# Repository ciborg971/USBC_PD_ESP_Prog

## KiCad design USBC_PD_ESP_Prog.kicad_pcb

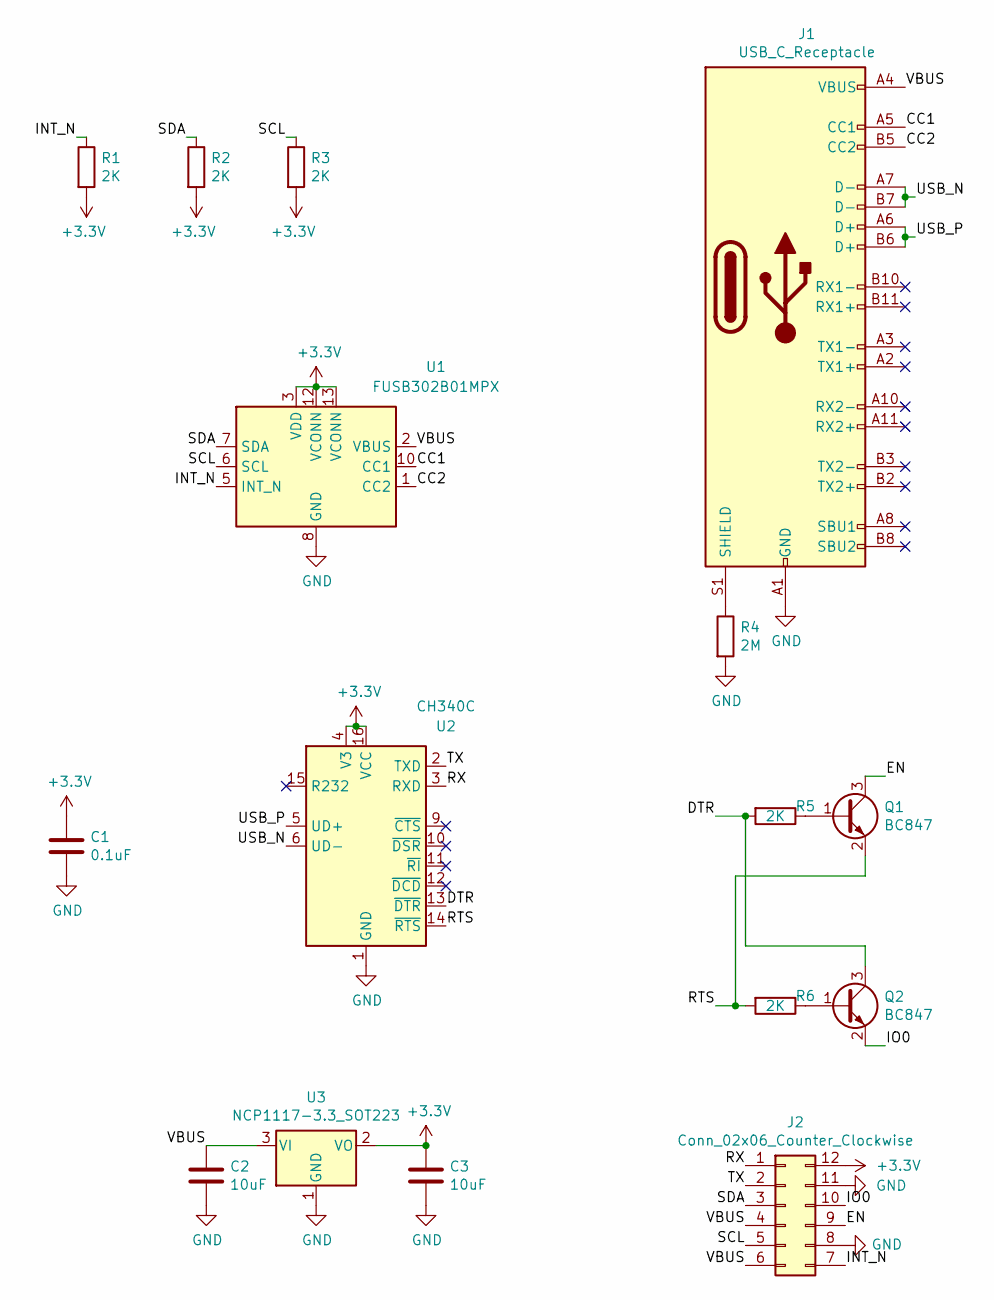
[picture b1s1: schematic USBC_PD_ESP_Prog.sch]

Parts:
C1: 0.1uF; C_0402_1005Metric
C2, C3: 10uF; C_0402_1005Metric
J1: USB_C_Receptacle; USB_C_Receptacle_Amphenol_12401610E4-2A
J2: Conn_02x06_Counter_Clockwise; PinHeader_2x06_P1.00mm_Vertical
Q1, Q2: BC847; SOT-23
R1, R2, R3, R5, R6: 2K; R_0201_0603Metric
R4: 2M; R_0201_0603Metric
U1: FUSB302B01MPX; WQFN-14-1EP_2.5x2.5mm_P0.5mm_EP1.45x1.45mm
U2: CH340C; SOIC-16_3.9x9.9mm_P1.27mm
U3: NCP1117-3.3_SOT223; SOT-223-3_TabPin2

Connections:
+3V3: C1.1, C3.1, J2.12, R1.2, R2.2, R3.2, U1.3 (VDD), U1.4 (VDD), U1.12 (VCONN), U1.13 (VCONN), U2.4 (V3), U2.16 (VCC), U3.2 (VO)
/CC1: J1.A5 (CC1), U1.10 (CC1), U1.11 (CC1)
/CC2: J1.B5 (CC2), U1.1 (CC2), U1.14 (CC2)
/DTR: Q2.3 (C), R5.2, U2.13 (~DTR)
/EN: J2.9, Q1.3 (C)
/INT_N: J2.7, R1.1, U1.5 (INT_N)
/IO0: J2.10, Q2.2 (E)
/RTS: Q1.2 (E), R6.2, U2.14 (~RTS)
/RX: J2.1, U2.3 (RXD)
/SCL: J2.5, R3.1, U1.6 (SCL)
/SDA: J2.3, R2.1, U1.7 (SDA)
/TX: J2.2, U2.2 (TXD)
/USB_N: J1.A7 (D-), J1.B7 (D-), U2.6 (UD-)
/USB_P: J1.A6 (D+), J1.B6 (D+), U2.5 (UD+)
/VBUS: C2.1, J1.A4 (VBUS), J1.A9 (VBUS), J1.B4 (VBUS), J1.B9 (VBUS), J2.4, J2.6, U1.2 (VBUS), U3.3 (VI)
GND: C1.2, C2.2, C3.2, J1.A1 (GND), J1.A12 (GND), J1.B1 (GND), J1.B12 (GND), J2.8, J2.11, R4.2, U1.8 (GND), U1.9 (GND), U1.15 (GND), U2.1 (GND), U3.1 (GND)
unnamed: J1.S1 (SHIELD), R4.1
unnamed: Q1.1 (B), R5.1
unnamed: Q2.1 (B), R6.1

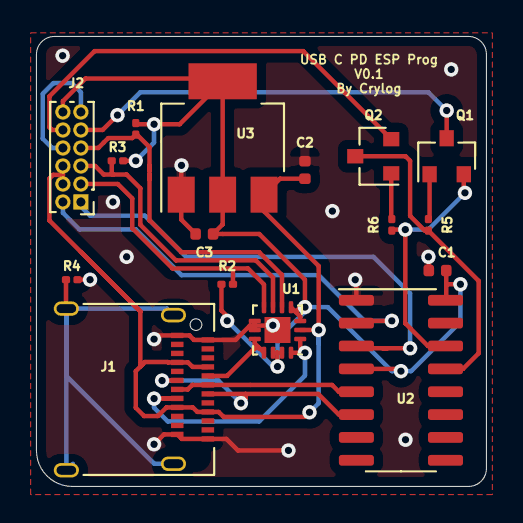
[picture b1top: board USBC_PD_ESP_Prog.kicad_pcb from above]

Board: 2 copper layers, 25.0 x 25.0 mm, 16 parts (0 on the bottom side), 19 nets.

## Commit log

2021-01-23 Add schematic and pcb design
2021-01-23 Doc
    Add doc for FUSB302, regulator, schematic from other project and the introduction to USB C from Microchip
2021-01-23 Clean silkscreen
